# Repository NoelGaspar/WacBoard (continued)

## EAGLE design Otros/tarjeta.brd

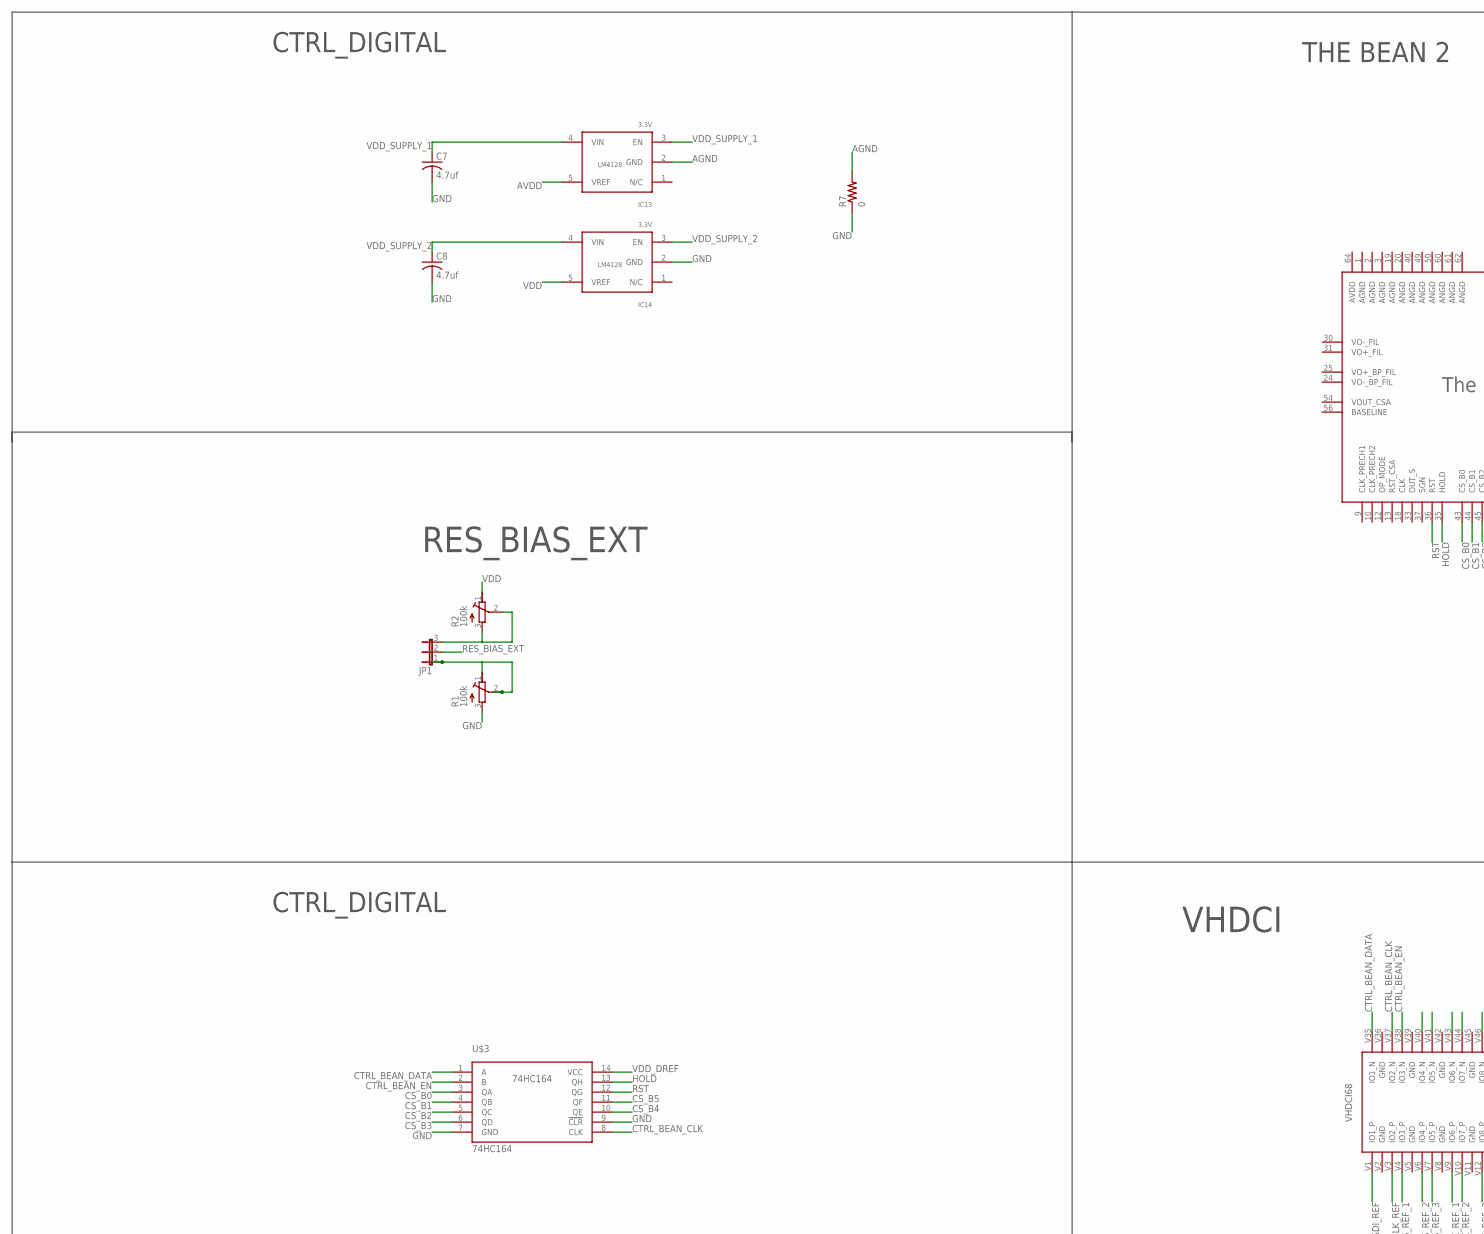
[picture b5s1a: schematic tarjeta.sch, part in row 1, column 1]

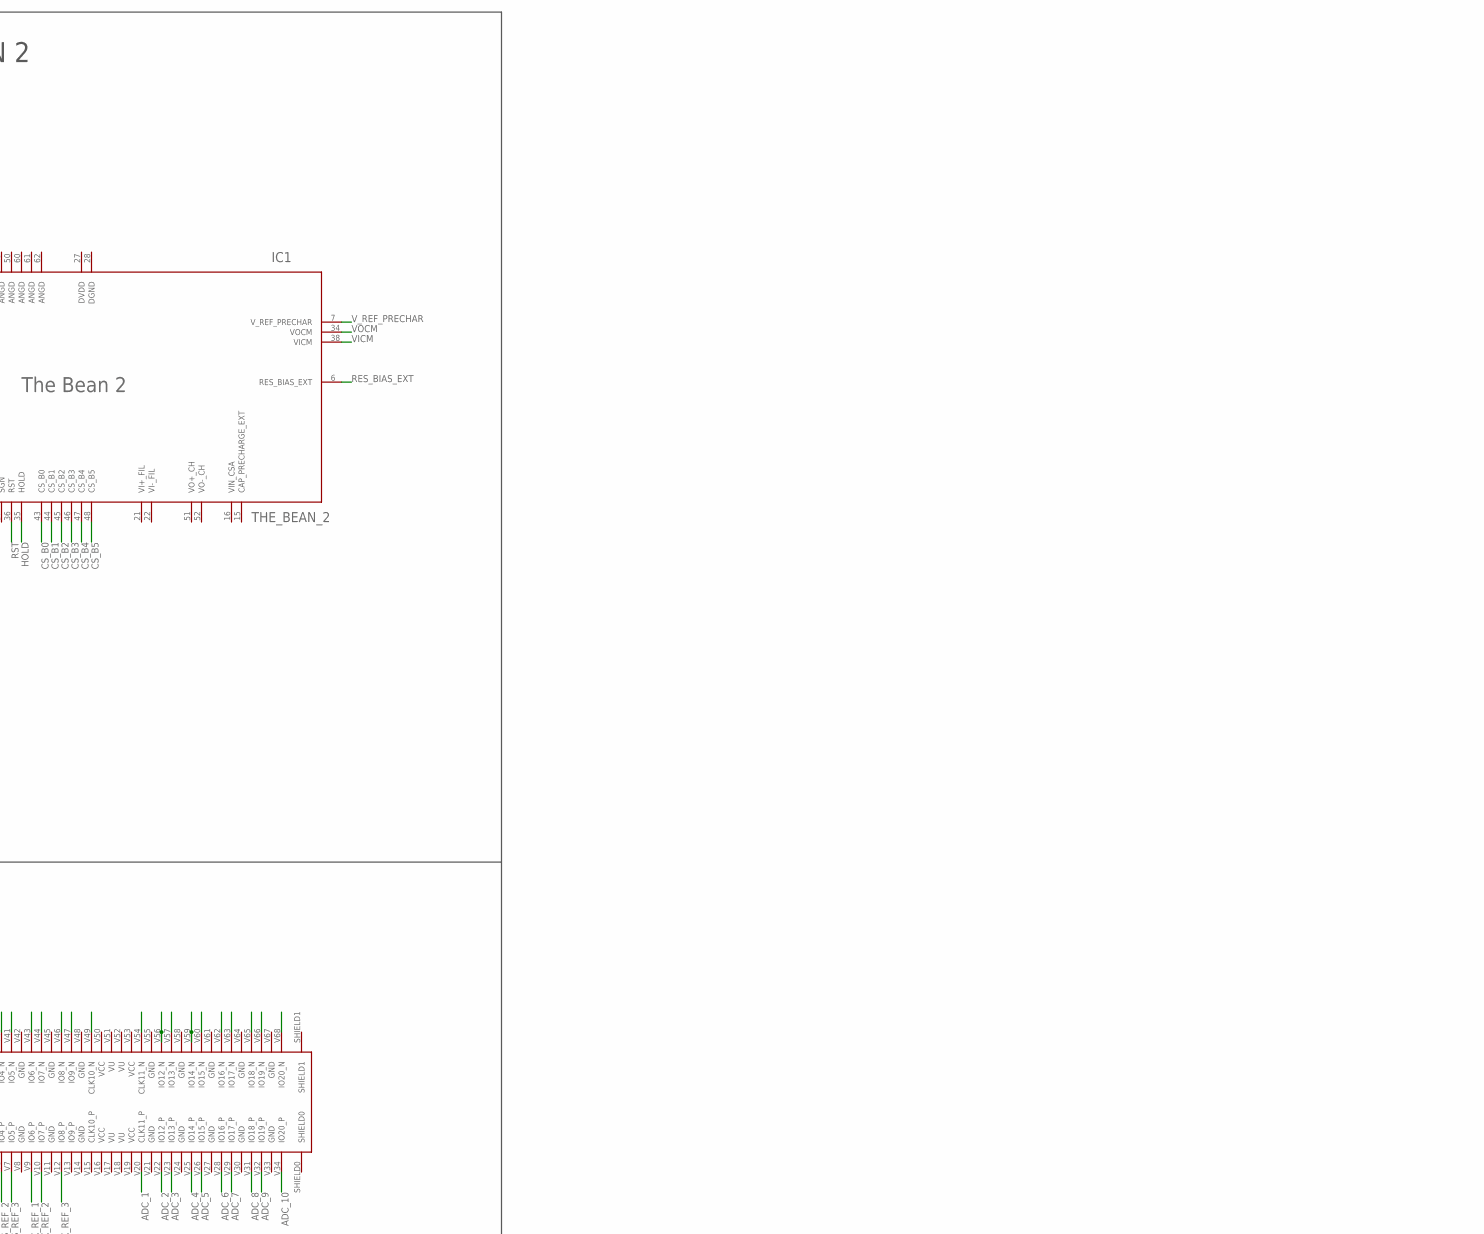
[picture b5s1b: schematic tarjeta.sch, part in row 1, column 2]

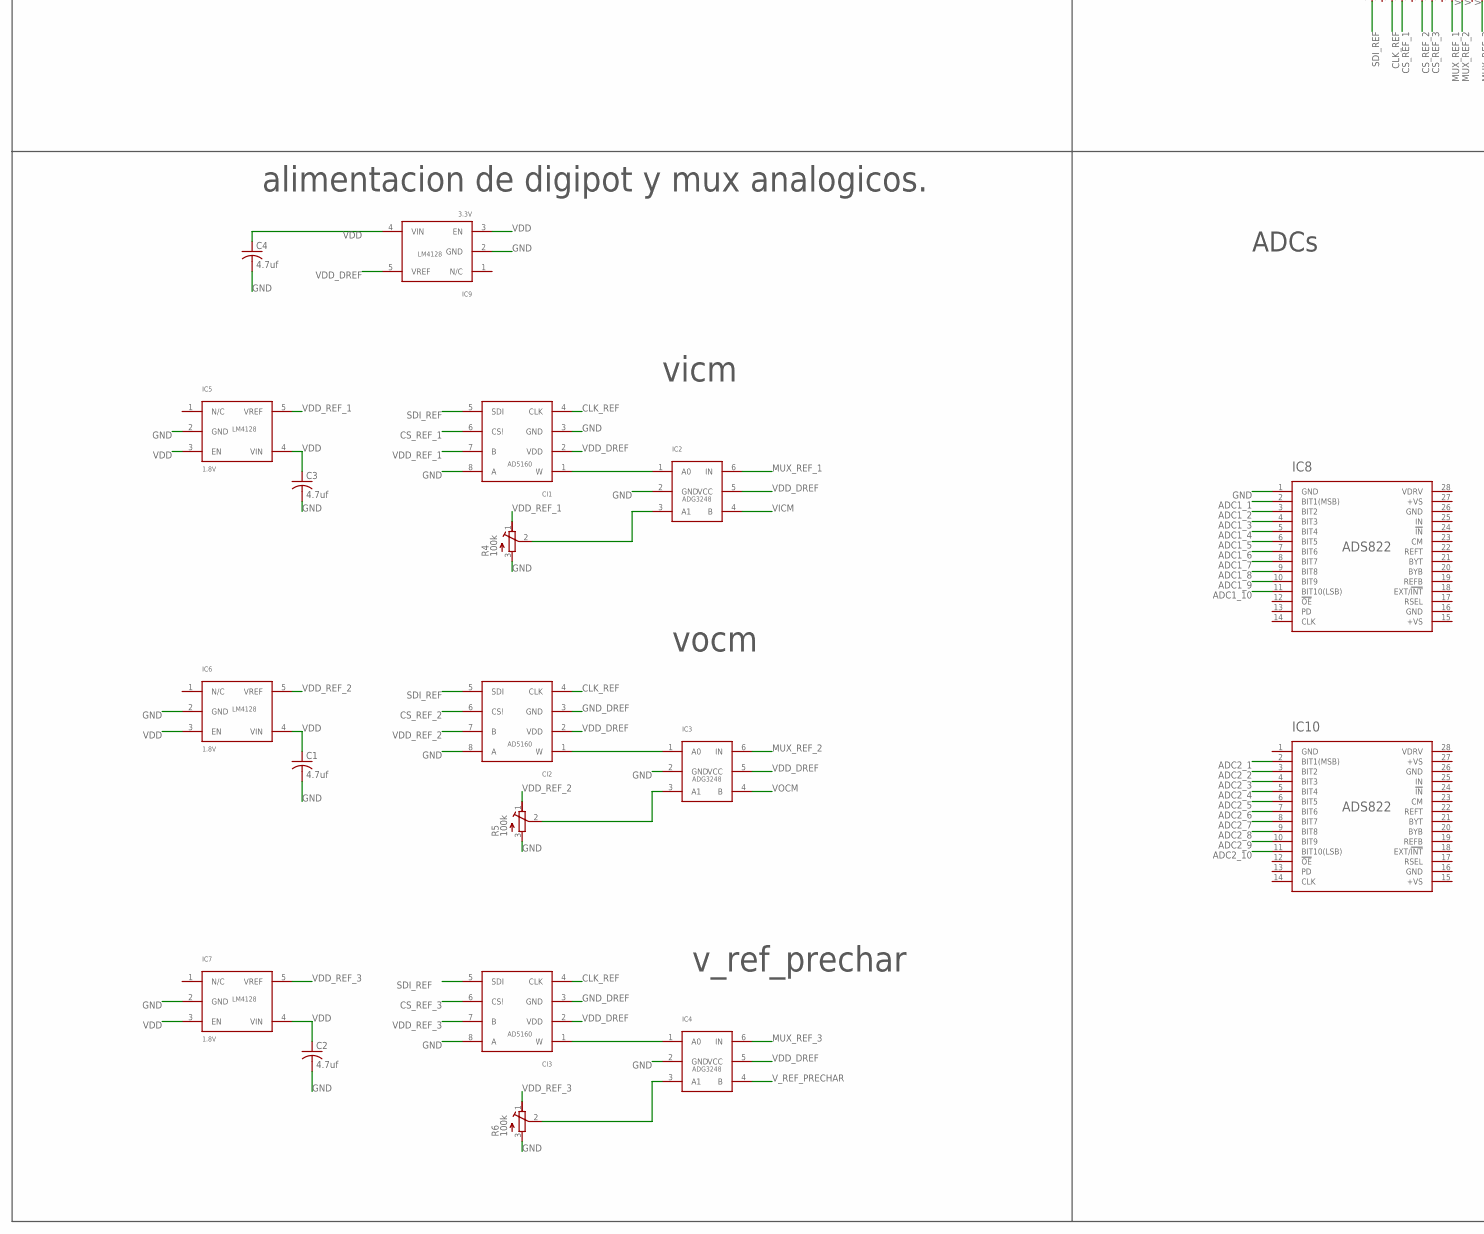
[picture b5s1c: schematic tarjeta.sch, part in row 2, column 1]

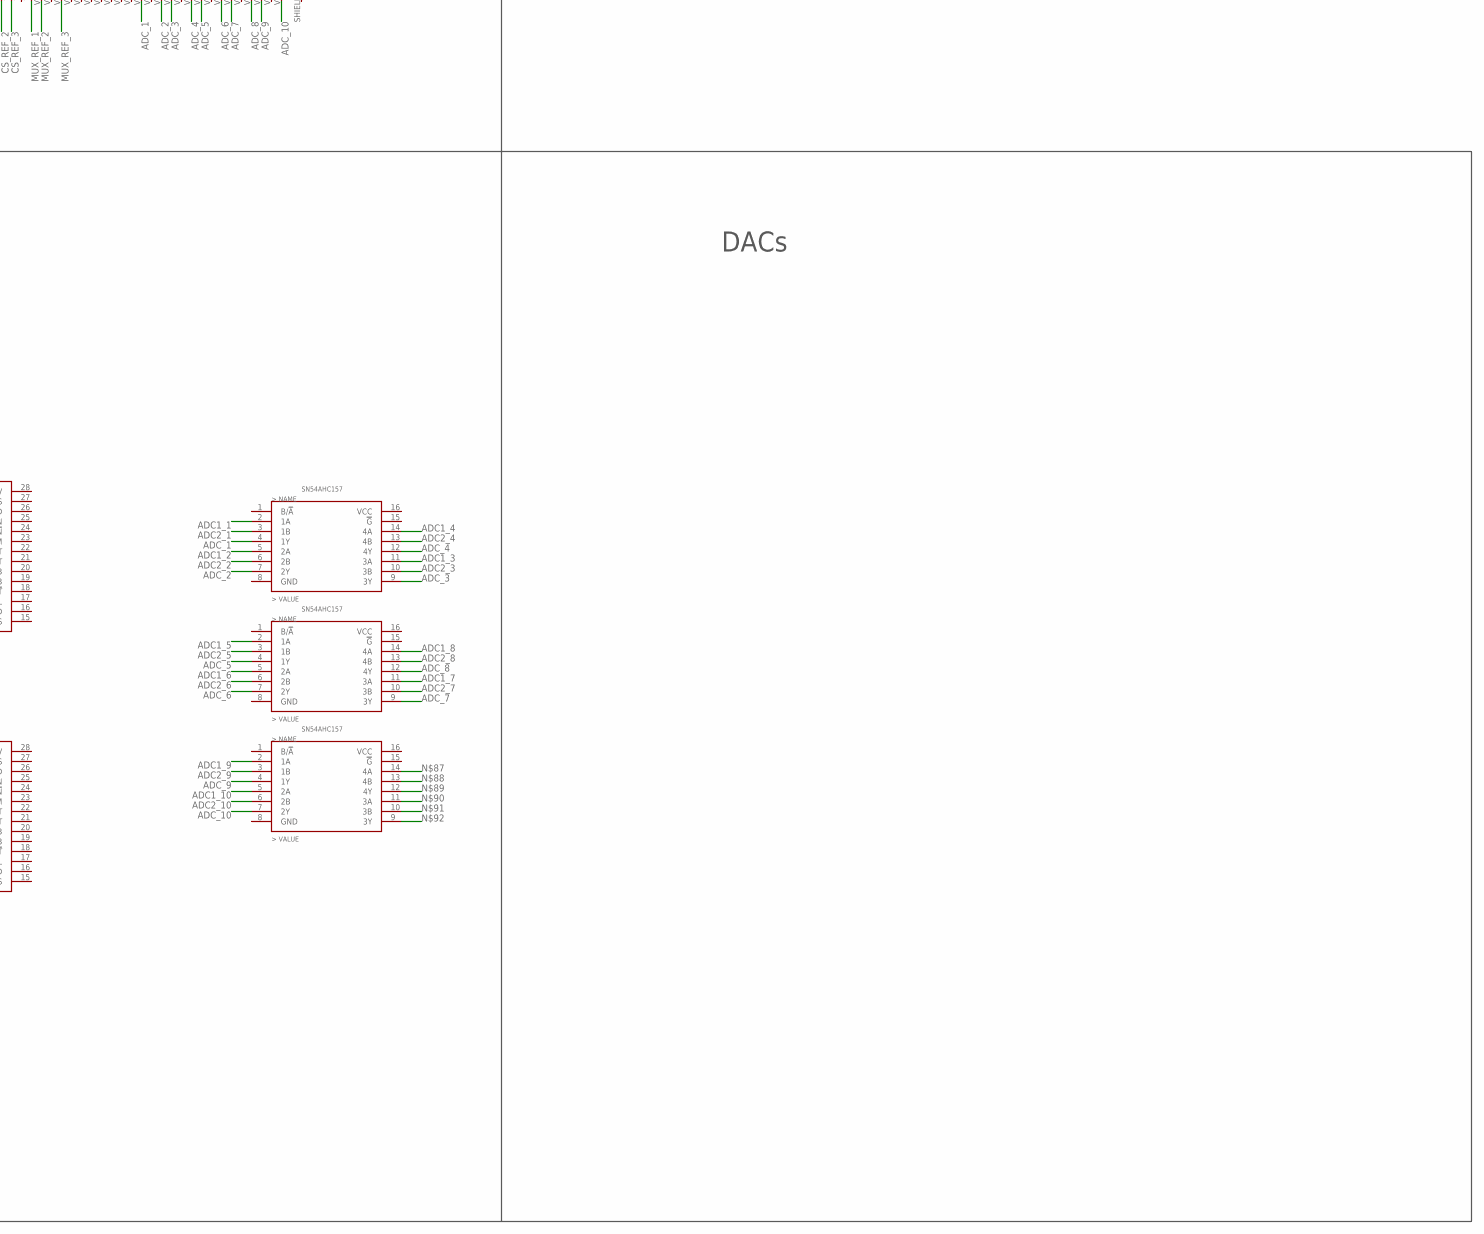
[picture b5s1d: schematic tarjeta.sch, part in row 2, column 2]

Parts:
C1, C2, C3, C4, C7, C8: 4.7uf; C0504
CI1, CI2, CI3: AD5160; SOT23-8
IC1: THE_BEAN_2; QFN64
IC2, IC3, IC4: ADG3248; SC70
IC5, IC6, IC7: 1.8V; SOT23-5L
IC8, IC10: ADS822; SSOP-28
IC9, IC13, IC14: 3.3V; SOT23-5L
IC11, IC12, IC15: SN54AHC157; TSSOP16
JP1: JP2E; JP2
R1, R2, R4, R5, R6: 100k; RTRIMT93YA
R7: 0; R0402
U$2: VHDCI68
U$3: 74HC164; TSSOP14

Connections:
ADC1_1: IC8.2 (BIT1(MSB)), IC11.2 (1A)
ADC1_2: IC8.3 (BIT2), IC11.5 (2A)
ADC1_3: IC8.4 (BIT3), IC11.11 (3A)
ADC1_4: IC8.5 (BIT4), IC11.14 (4A)
ADC1_5: IC8.6 (BIT5), IC12.2 (1A)
ADC1_6: IC8.7 (BIT6), IC12.5 (2A)
ADC1_7: IC8.8 (BIT7), IC12.11 (3A)
ADC1_8: IC8.9 (BIT8), IC12.14 (4A)
ADC1_9: IC8.10 (BIT9), IC15.2 (1A)
ADC1_10: IC8.11 (BIT10(LSB)), IC15.5 (2A)
ADC2_1: IC10.2 (BIT1(MSB)), IC11.3 (1B)
ADC2_2: IC10.3 (BIT2), IC11.6 (2B)
ADC2_3: IC10.4 (BIT3), IC11.10 (3B)
ADC2_4: IC10.5 (BIT4), IC11.13 (4B)
ADC2_5: IC10.6 (BIT5), IC12.3 (1B)
ADC2_6: IC10.7 (BIT6), IC12.6 (2B)
ADC2_7: IC10.8 (BIT7), IC12.10 (3B)
ADC2_8: IC10.9 (BIT8), IC12.13 (4B)
ADC2_9: IC10.10 (BIT9), IC15.3 (1B)
ADC2_10: IC10.11 (BIT10(LSB)), IC15.6 (2B)
ADC_1: IC11.4 (1Y), U$2.V20 (CLK11_P)
ADC_2: IC11.7 (2Y), U$2.V22 (IO12_P)
ADC_3: IC11.9 (3Y), U$2.V23 (IO13_P)
ADC_4: IC11.12 (4Y), U$2.V25 (IO14_P)
ADC_5: IC12.4 (1Y), U$2.V26 (IO15_P)
ADC_6: IC12.7 (2Y), U$2.V28 (IO16_P)
ADC_7: IC12.9 (3Y), U$2.V29 (IO17_P)
ADC_8: IC12.12 (4Y), U$2.V31 (IO18_P)
ADC_9: IC15.4 (1Y), U$2.V32 (IO19_P)
ADC_10: IC15.7 (2Y), U$2.V34 (IO20_P)
AGND: IC1.1 (AGND), IC1.2 (AGND), IC1.3 (AGND), IC1.19 (AGND), IC13.2 (GND), R7.2
ANGD: IC1.20 (ANGD), IC1.40 (ANGD), IC1.49 (ANGD), IC1.50 (ANGD), IC1.60 (ANGD), IC1.61 (ANGD), IC1.62 (ANGD)
AVDD: IC1.64 (AVDD), IC13.5 (VREF)
CLK_REF: CI1.4 (CLK), CI2.4 (CLK), CI3.4 (CLK), U$2.V3 (IO2_P)
CS_B0: IC1.43 (CS_B0), U$3.3 (QA)
CS_B1: IC1.44 (CS_B1), U$3.4 (QB)
CS_B2: IC1.45 (CS_B2), U$3.5 (QC)
CS_B3: IC1.46 (CS_B3), U$3.6 (QD)
CS_B4: IC1.47 (CS_B4), U$3.10 (QE)
CS_B5: IC1.48 (CS_B5), U$3.11 (QF)
CS_REF_1: CI1.6 (CS!), U$2.V4 (IO3_P)
CS_REF_2: CI2.6 (CS!), U$2.V6 (IO4_P)
CS_REF_3: CI3.6 (CS!), U$2.V7 (IO5_P)
CTRL_BEAN_CLK: U$2.V37 (IO2_N), U$3.8 (CLK)
CTRL_BEAN_DATA: U$2.V35 (IO1_N), U$3.1 (A)
CTRL_BEAN_EN: U$2.V38 (IO3_N), U$3.2 (B)
DGND: IC1.28 (DGND)
DVDD: IC1.27 (DVDD)
GND: C1.2, C2.2, C3.2, C4.2, C7.2, C8.2, CI1.3 (GND), CI1.8 (A), CI2.8 (A), CI3.8 (A), IC2.2 (GND), IC3.2 (GND), IC4.2 (GND), IC5.2 (GND), IC6.2 (GND), IC7.2 (GND), IC8.1 (GND), IC9.2 (GND), IC14.2 (GND), R1.3 (A), R4.3 (A), R5.3 (A), R6.3 (A), R7.1, U$3.7 (GND), U$3.9 (!CLR)
GND_DREF: CI2.3 (GND), CI3.3 (GND)
HOLD: IC1.35 (HOLD), U$3.13 (QH)
MUX_REF_1: IC2.6 (IN), U$2.V9 (IO6_P)
MUX_REF_2: IC3.6 (IN), U$2.V10 (IO7_P)
MUX_REF_3: IC4.6 (IN), U$2.V12 (IO8_P)
unnamed: JP1.3, R2.2 (S), R2.3 (A)
unnamed: JP1.1, R1.1 (E), R1.2 (S)
unnamed: CI1.1 (W), IC2.1 (A0)
unnamed: IC2.3 (A1), R4.2 (S)
unnamed: CI2.1 (W), IC3.1 (A0)
unnamed: CI3.1 (W), IC4.1 (A0)
unnamed: IC4.3 (A1), R6.2 (S)
unnamed: IC3.3 (A1), R5.2 (S)
RES_BIAS_EXT: IC1.6 (RES_BIAS_EXT), JP1.2
RST: IC1.36 (RST), U$3.12 (QG)
SDI_REF: CI1.5 (SDI), CI2.5 (SDI), CI3.5 (SDI), U$2.V1 (IO1_P)
VCC: U$2.V16 (VCC), U$2.V19 (VCC), U$2.V50 (VCC), U$2.V53 (VCC)
VDD: C1.1, C2.1, C3.1, C4.1, IC5.3 (EN), IC5.4 (VIN), IC6.3 (EN), IC6.4 (VIN), IC7.3 (EN), IC7.4 (VIN), IC9.3 (EN), IC9.4 (VIN), IC14.5 (VREF), R2.1 (E)
VDD_DREF: CI1.2 (VDD), CI2.2 (VDD), CI3.2 (VDD), IC2.5 (VCC), IC3.5 (VCC), IC4.5 (VCC), IC9.5 (VREF), U$3.14 (VCC)
VDD_REF_1: CI1.7 (B), IC5.5 (VREF), R4.1 (E)
VDD_REF_2: CI2.7 (B), IC6.5 (VREF), R5.1 (E)
VDD_REF_3: CI3.7 (B), IC7.5 (VREF), R6.1 (E)
VDD_SUPPLY_1: C7.1, IC13.3 (EN), IC13.4 (VIN)
VDD_SUPPLY_2: C8.1, IC14.3 (EN), IC14.4 (VIN)
VICM: IC1.38 (VICM), IC2.4 (B)
VOCM: IC1.34 (VOCM), IC3.4 (B)
VU: U$2.V17 (VU), U$2.V18 (VU), U$2.V51 (VU), U$2.V52 (VU)
V_REF_PRECHAR: IC1.7 (V_REF_PRECHAR), IC4.4 (B)

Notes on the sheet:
vicm
vocm
v_ref_prechar
alimentacion de digipot y mux analogicos.
VHDCI
RES_BIAS_EXT
CTRL_DIGITAL
ADCs
THE BEAN 2
DACs

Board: 2 copper layers, 33 parts (0 on the bottom side), 75 nets, no tracks yet.

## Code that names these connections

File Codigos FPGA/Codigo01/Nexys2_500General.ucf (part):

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#NET "PS2D"        LOC = "P11";   # Bank = 2, Pin name = IO_L18P_2, Type = I/O,                        Sch name = PS2D

## FX2 connector
NET "SDI_REF"      LOC = "B4";  	#pio0 # Bank = 0, Pin name = IO_L24N_0, Type = I/O,                        Sch name = R-IO1
NET "CS_REF3"      LOC = "A4";  	#pio1 # Bank = 0, Pin name = IO_L24P_0, Type = I/O,                        Sch name = R-IO2
NET "CLK_REF"      LOC = "C3";  	#pio2 # Bank = 0, Pin name = IO_L25P_0, Type = I/O,                        Sch name = R-IO3
NET "MUX_REF3"     LOC = "C4";  	#pio3 # Bank = 0, Pin name = IO, Type = I/O,                               Sch name = R-IO4
NET "CS_REF2"      LOC = "B6";  	#pio4 # Bank = 0, Pin name = IO_L20P_0, Type = I/O,                        Sch name = R-IO5
NET "CS_REF1"      LOC = "D5";  	#pio5	# Bank = 0, Pin name = IO_L23N_0/VREF_0, Type = VREF,                Sch name = R-IO6
NET "MUX_REF1"     LOC = "C5"; 	#pio6 # Bank = 0, Pin name = IO_L23P_0, Type = I/O,                        Sch name = R-IO7
NET "MUX_REF2"     LOC = "F7"; 	#pio7 # Bank = 0, Pin name = IO_L19P_0, Type = I/O,                        Sch name = R-IO8
NET "CS_DAC"     	 LOC = "E7";	#pio8	# Bank = 0, Pin name = IO_L19N_0/VREF_0, Type = VREF,                Sch name = R-IO9
NET "SDI_DAC"      LOC = "A6";   #pio9 # Bank = 0, Pin name = IO_L20N_0, Type = I/O,                        Sch name = R-IO10
NET "CLK_DAC"      LOC = "C7";   #pio10 # Bank = 0, Pin name = IO_L18P_0, Type = I/O,                        Sch name = R-IO11
#NET "PIO<11>"     LOC = "F8";    # Bank = 0, Pin name = IO_L17N_0, Type = I/O,                        Sch name = R-IO12
NET "SDO_ADC2"     LOC = "D7";    # Bank = 0, Pin name = IO_L18N_0/VREF_0, Type = VREF,                Sch name = R-IO13
NET "CS_ADC2"     LOC = "E8";    # Bank = 0, Pin name = IO_L17P_0, Type = I/O,                        Sch name = R-IO14
NET "CLK_ADC2"     LOC = "E9";    # Bank = 0, Pin name = IO_L15P_0, Type = I/O,                        Sch name = R-IO15
NET "DMUX_EN"     LOC = "C9";    # Bank = 0, Pin name = IO_L14P_0/GCLK10, Type = GCLK,                Sch name = R-IO16
NET "DMUX_SEL"     LOC = "A8";    # Bank = 0, Pin name = IO, Type = I/O,                               Sch name = R-IO17
#NET "PIO<17>"     LOC = "G9";    # Bank = 0, Pin name = IO, Type = I/O,                               Sch name = R-IO18
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#NET "PIO<34>"     LOC = "A14";   # Bank = 0, Pin name = IO_L04N_0, Type = I/O,                        Sch name = R-IO35
#NET "PIO<35>"     LOC = "C14";   # Bank = 0, Pin name = IO_L03N_0/VREF_0, Type = VREF,                Sch name = R-IO36
#NET "PIO<36>"     LOC = "D14";   # Bank = 0, Pin name = IO_L03P_0, Type = I/O,                        Sch name = R-IO37
NET "SDO_ADC1"     LOC = "B14";   # Bank = 0, Pin name = IO_L04P_0, Type = I/O,                        Sch name = R-IO38
NET "CS_ADC1"     LOC = "A16";   # Bank = 0, Pin name = IO_L01N_0, Type = I/O,                        Sch name = R-IO39
NET "CLK_ADC1"     LOC = "B16";   # Bank = 0, Pin name = IO_L01P_0, Type = I/O,                        Sch name = R-IO40

## 12 pin connectors
##JA
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
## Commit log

2018-12-27 git start. upload existing files
2018-12-27 compiling
2019-01-03 setting git and texmaker and miktex
